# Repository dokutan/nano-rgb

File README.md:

# nano-rgb
2-channel Arduino Nano common anode RGB strip controller

## Parts
- 1 Arduino Nano
- 4 Pushbuttons (optional)
- per channel:
  - 3 220Ω Resistors (this value doesn't really matter)
  - 3 BS170 MOSFETs
  - Screw terminals or pin headers (optional)
  - pin headers and jumper to power the Arduino from the LED power supply (optional)
  
  **Warning:** don't exceed the current limits of the MOSFET, and if you are trying to supply the Arduino from the power supply instead of USB, make sure the it can handle the voltage.
  
## Software
### Arduino
- arduino-code/example1: a simple example to control the color with the onboard pushbuttons
- arduino-code/serial-in: reads the color values over serial

### PC
- pc-code/uleds-bridge: this program adds support for the nano-rgb to the linux led subsystem. See pc-code/uleds-bridge/README.md for details.
- pc-code/nano-rgb-color: Set the color directly over serial. See pc-code/nano-rgb-color/README.md for details.

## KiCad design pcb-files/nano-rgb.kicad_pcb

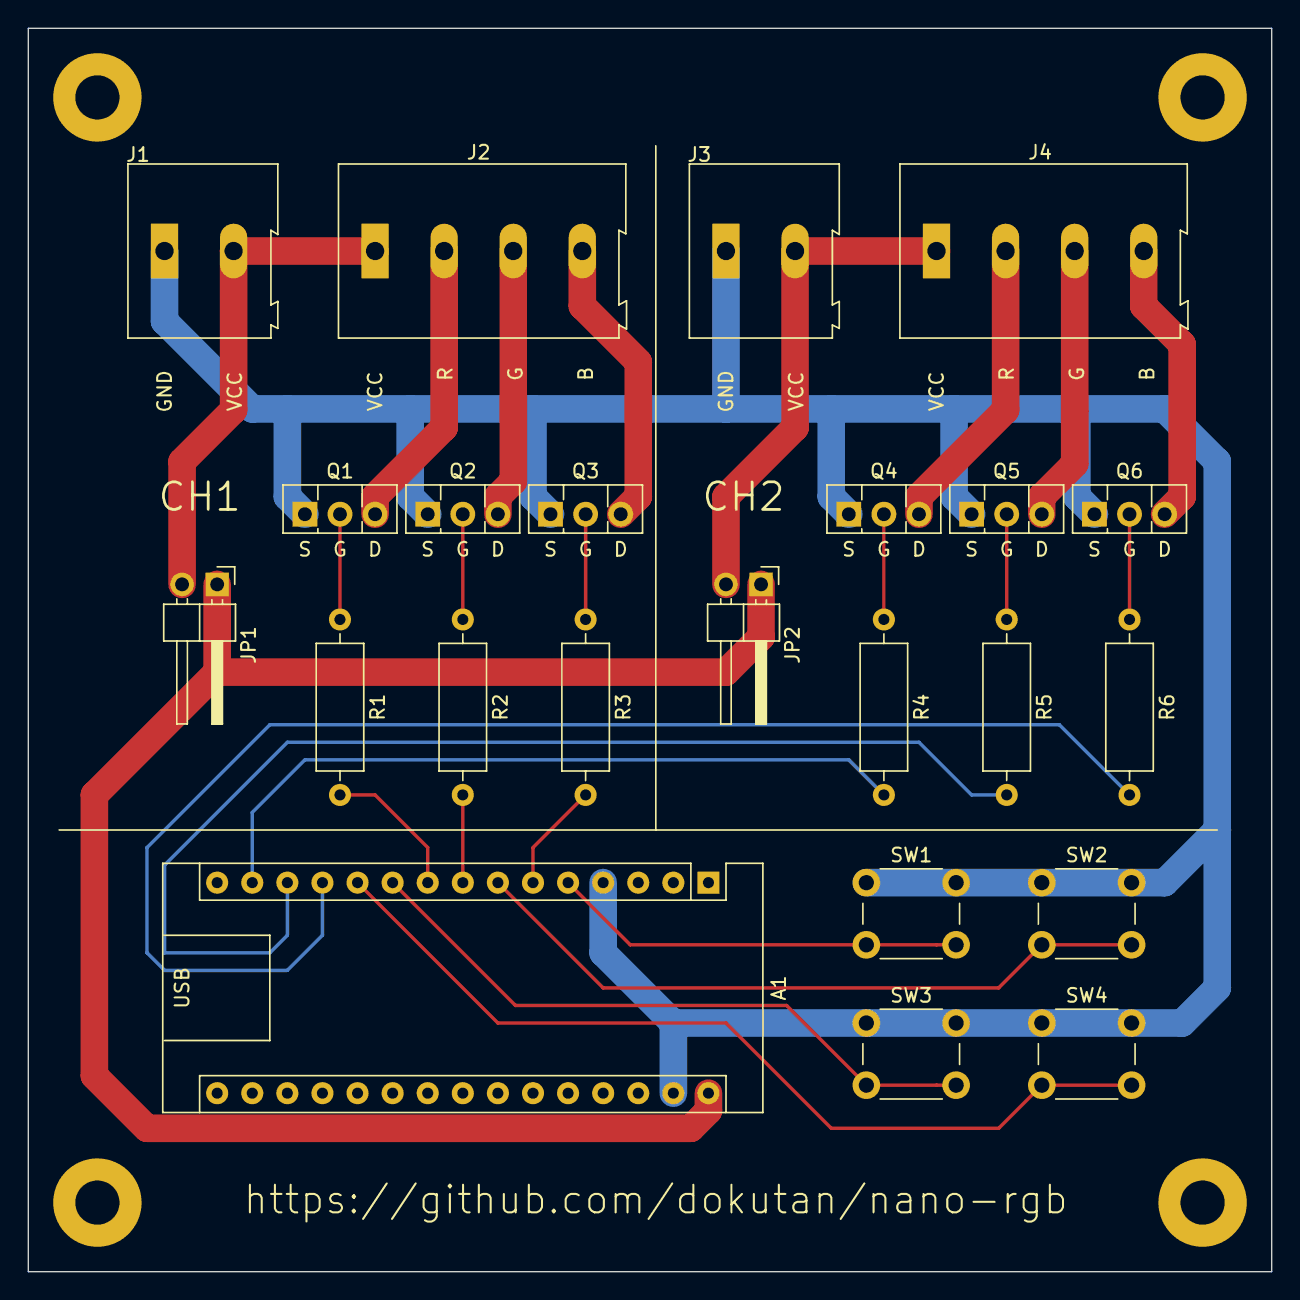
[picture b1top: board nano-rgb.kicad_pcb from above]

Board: 2 copper layers, 90.0 x 90.0 mm, 23 parts (0 on the bottom side), 26 nets.

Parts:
A1: Arduino_Nano_v3.x; Arduino_Nano
J1, J3: Screw_Terminal_01x02; TerminalBlock_Altech_AK300-2_P5.00mm
J2, J4: Screw_Terminal_01x04; TerminalBlock_Altech_AK300-4_P5.00mm
JP1, JP2: Jumper_2_Open; PinHeader_1x02_P2.54mm_Horizontal
Q1, Q2, Q3, Q4, Q5, Q6: 2N7000; TO-126-3_Vertical
R1, R2, R3, R4, R5, R6: R; R_Axial_DIN0309_L9.0mm_D3.2mm_P12.70mm_Horizontal
SW1, SW2, SW3, SW4: SW_Push; SW_PUSH_6mm

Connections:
unnamed: A1.5, SW1.2
unnamed: A1.6, R3.2
unnamed: A1.7, SW2.2
unnamed: A1.8, R2.2
unnamed: A1.9, R1.2
unnamed: A1.10, SW3.2
unnamed: A1.11, SW4.2
unnamed: A1.12, R6.2
unnamed: A1.13, R5.2
unnamed: A1.14, R4.2
unnamed: A1.4, A1.29, J1.1, J3.1, Q1.1, Q2.1, Q3.1, Q4.1, Q5.1, Q6.1, SW1.1, SW2.1, SW3.1, SW4.1
unnamed: A1.30, JP1.1, JP2.1
unnamed: J1.2, J2.1, JP1.2
unnamed: J2.2, Q1.3
unnamed: J2.3, Q2.3
unnamed: J2.4, Q3.3
unnamed: J3.2, J4.1, JP2.2
unnamed: J4.2, Q4.3
unnamed: J4.3, Q5.3
unnamed: J4.4, Q6.3
unnamed: Q1.2, R1.1
unnamed: Q2.2, R2.1
unnamed: Q3.2, R3.1
unnamed: Q4.2, R4.1
unnamed: Q5.2, R5.1
unnamed: Q6.2, R6.1

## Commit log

2019-11-07 Add files via upload
    Add pcb files
2019-11-09 Add Arduino example
2019-11-29 Create LICENSE
    Switch from GPLv3 to GPLv2
2019-11-29 Add serial-in arduino code and uleds-bridge
2019-11-29 Add arduino serial-in and uleds-bridge for really now
2019-11-29 Add 2 channel support to uleds-bridge
2019-11-29 Add makefile for uleds-bridge
2019-11-29 Update README.md for uleds-bridge
2019-12-02 Add nano-rgb-color program
